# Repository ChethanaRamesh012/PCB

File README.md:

Designed a high-frequency PLL circuit on a two-layer PCB using KiCad, optimizing signal integrity and minimizing phase noise for RF 
applications.
Implemented precise trace routing, controlled impedance, and grounding strategies to enhance frequency stability and reduce 
electromagnetic interference (EMI).

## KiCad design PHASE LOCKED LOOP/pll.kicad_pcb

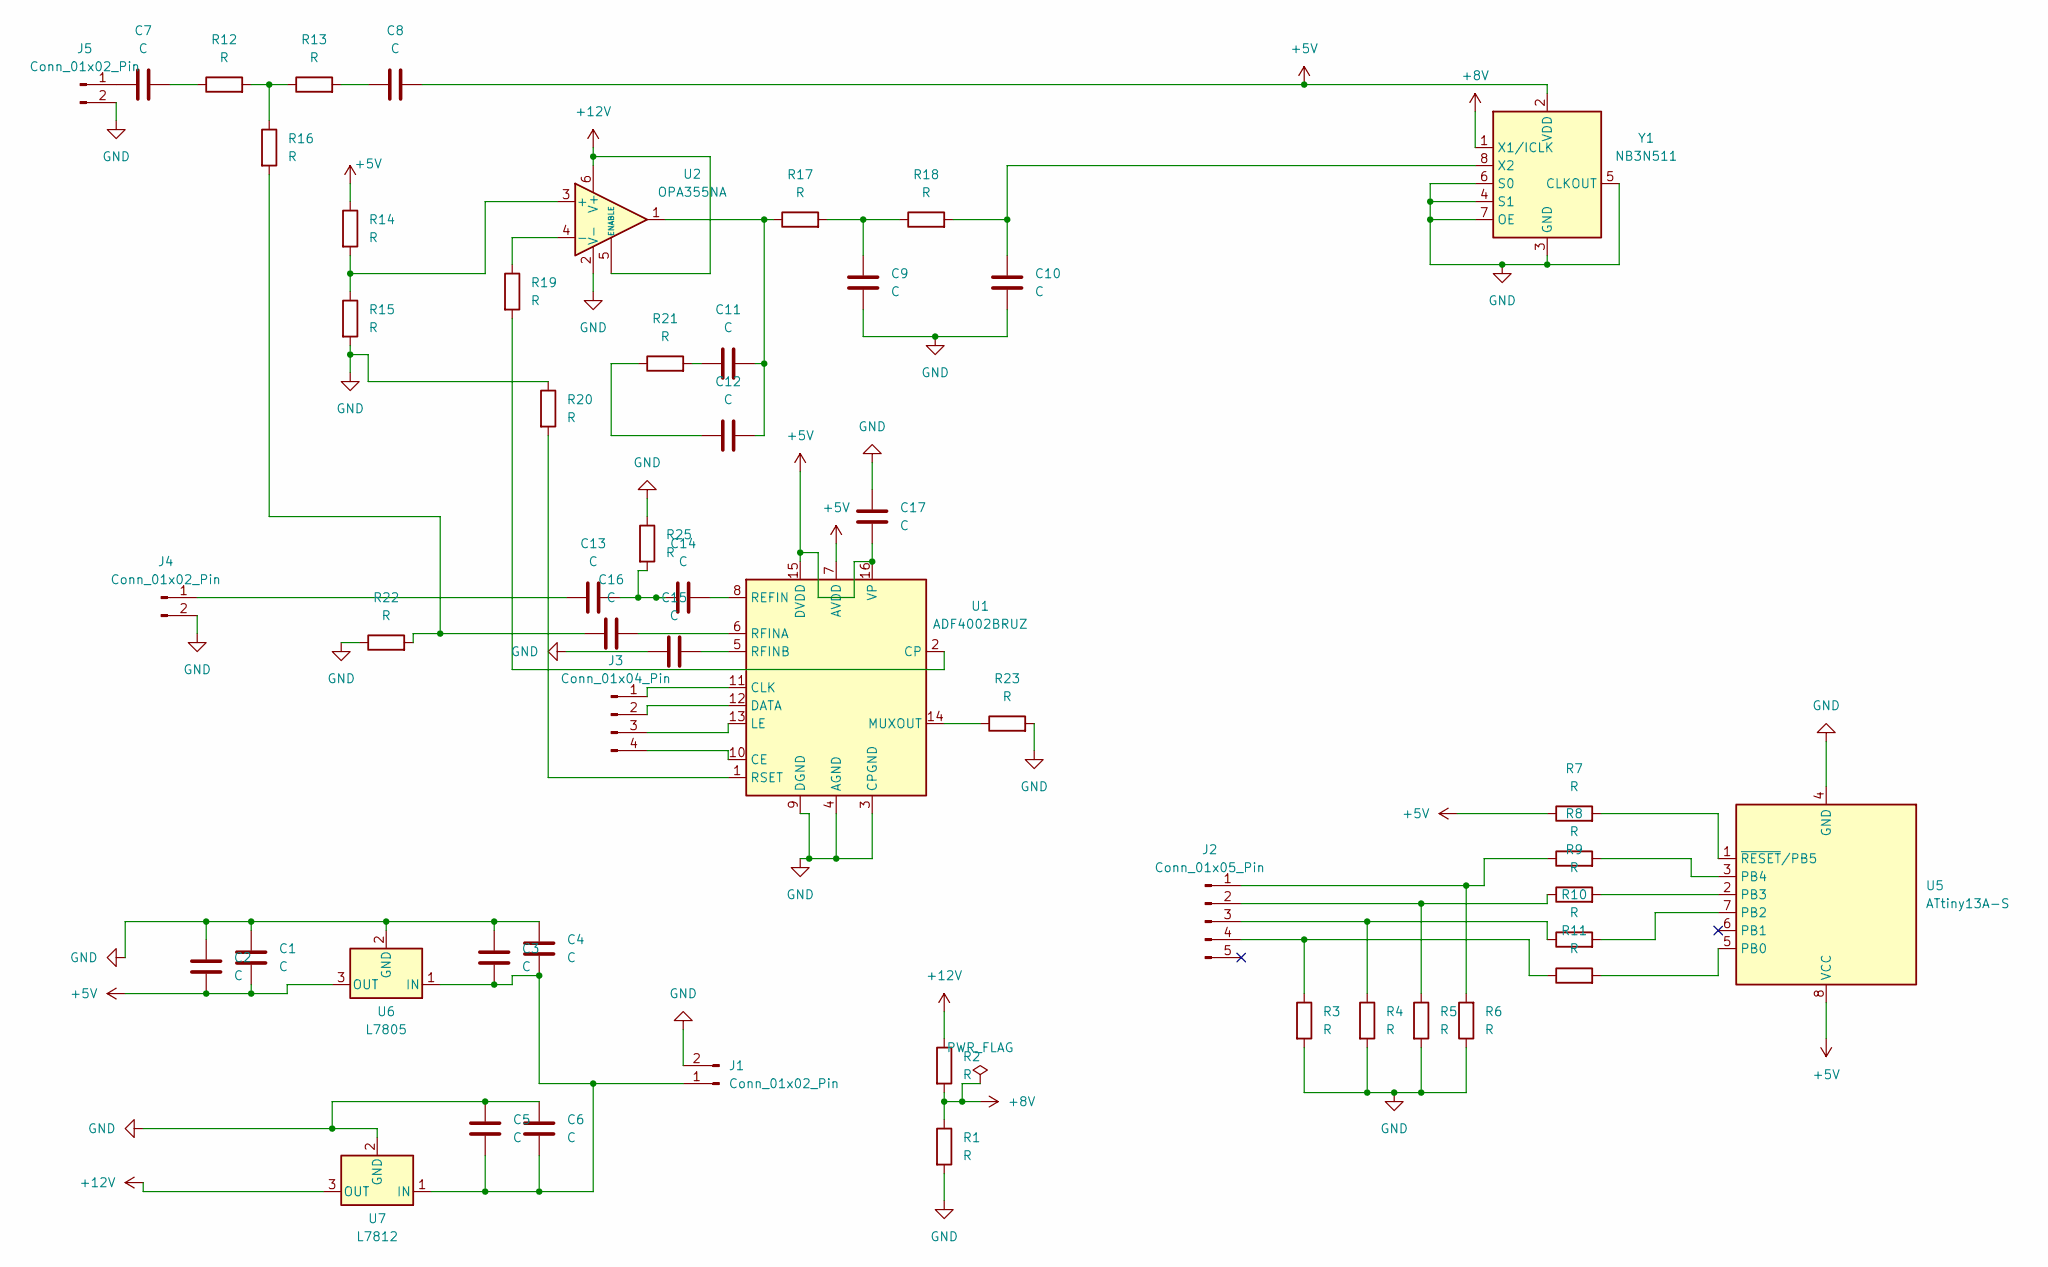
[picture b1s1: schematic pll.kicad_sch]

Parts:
C1, C2, C3, C4, C5, C6, C7, C8, C9, C10, C11, C12, C13, C14, C15, C16, C17: C; C_Axial_L3.8mm_D2.6mm_P7.50mm_Horizontal
J1: Conn_01x02_Pin; PinHeader_1x02_P2.00mm_Vertical
J2: Conn_01x05_Pin; PinHeader_1x05_P1.27mm_Vertical
J3: Conn_01x04_Pin; PinHeader_1x04_P1.00mm_Vertical
J4, J5: Conn_01x02_Pin; PinHeader_1x02_P1.00mm_Vertical
R1, R2, R3, R4, R5, R6, R7, R8, R9, R10, R11, R12, R13, R14, R15, R16, R17, R18, R19, R20, R21, R22, R23, R25: R; R_Axial_DIN0204_L3.6mm_D1.6mm_P1.90mm_Vertical
U1: ADF4002BRUZ; TSSOP-16_4.4x5mm_P0.65mm
U2: OPA355NA; SOT-23-6
U5: ATtiny13A-S; SOIC-8_5.3x5.3mm_P1.27mm
U6: L7805; TO-220F-3_Vertical
U7: L7812; TO-220F-3_Vertical
Y1: NB3N511; SOIC-8_3.9x4.9mm_P1.27mm

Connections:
+8V: R1.1, R2.2, Y1.1 (X1/ICLK)
+12V: R2.1, U2.5 (ENABLE), U2.6 (V+), U7.3 (OUT)
GND: C1.1, C2.1, C3.1, C4.1, C5.1, C6.1, C9.1, C10.1, C15.1, C17.2, J1.2, J4.2, J5.2, R1.2, R3.2, R4.2, R5.2, R6.1, R15.2, R20.1, R22.1, R23.2, R25.1, U1.3 (CPGND), U1.4 (AGND), U1.9 (DGND), U2.2 (V-), U5.4 (GND), U6.2 (GND), U7.2 (GND), Y1.3 (GND), Y1.4 (S1), Y1.5 (CLKOUT), Y1.6 (S0), Y1.7 (OE)
unnamed: C7.2, R12.1
unnamed: C8.1, R13.2
unnamed: C9.2, R17.2, R18.1
unnamed: C11.1, R21.2
unnamed: C11.2, C12.2, R17.1, U2.1
unnamed: C12.1, R21.1
unnamed: C13.2, C14.1, R25.2
unnamed: C16.1, R16.2, R22.2
unnamed: C3.2, C4.2, C5.2, C6.2, J1.1, U6.1 (IN), U7.1 (IN)
unnamed: J2.1, R6.2, R8.1
unnamed: J2.2, R5.1, R9.1
unnamed: J2.3, R4.1, R10.1
unnamed: J2.4, R3.1, R11.1
unnamed: J3.1, U1.11 (CLK)
unnamed: J3.2, U1.12 (DATA)
unnamed: J3.3, U1.13 (LE)
unnamed: J3.4, U1.10 (CE)
unnamed: C13.1, J4.1
unnamed: C7.1, J5.1
unnamed: R12.2, R13.1, R16.1
unnamed: R19.2, U1.2 (CP)
unnamed: R23.1, U1.14 (MUXOUT)
unnamed: C14.2, U1.8 (REFIN)
unnamed: C16.2, U1.6 (RFINA)
unnamed: C15.2, U1.5 (RFINB)
unnamed: R20.2, U1.1 (RSET)
unnamed: R14.2, R15.1, U2.3 (+)
unnamed: R19.1, U2.4 (-)
unnamed: R11.2, U5.5 (PB0)
unnamed: R10.2, U5.7 (PB2)
unnamed: R9.2, U5.2 (PB3)
unnamed: R8.2, U5.3 (PB4)
unnamed: R7.2, U5.1 (~RESET/PB5)
unnamed: C10.2, R18.2, Y1.8 (X2)

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
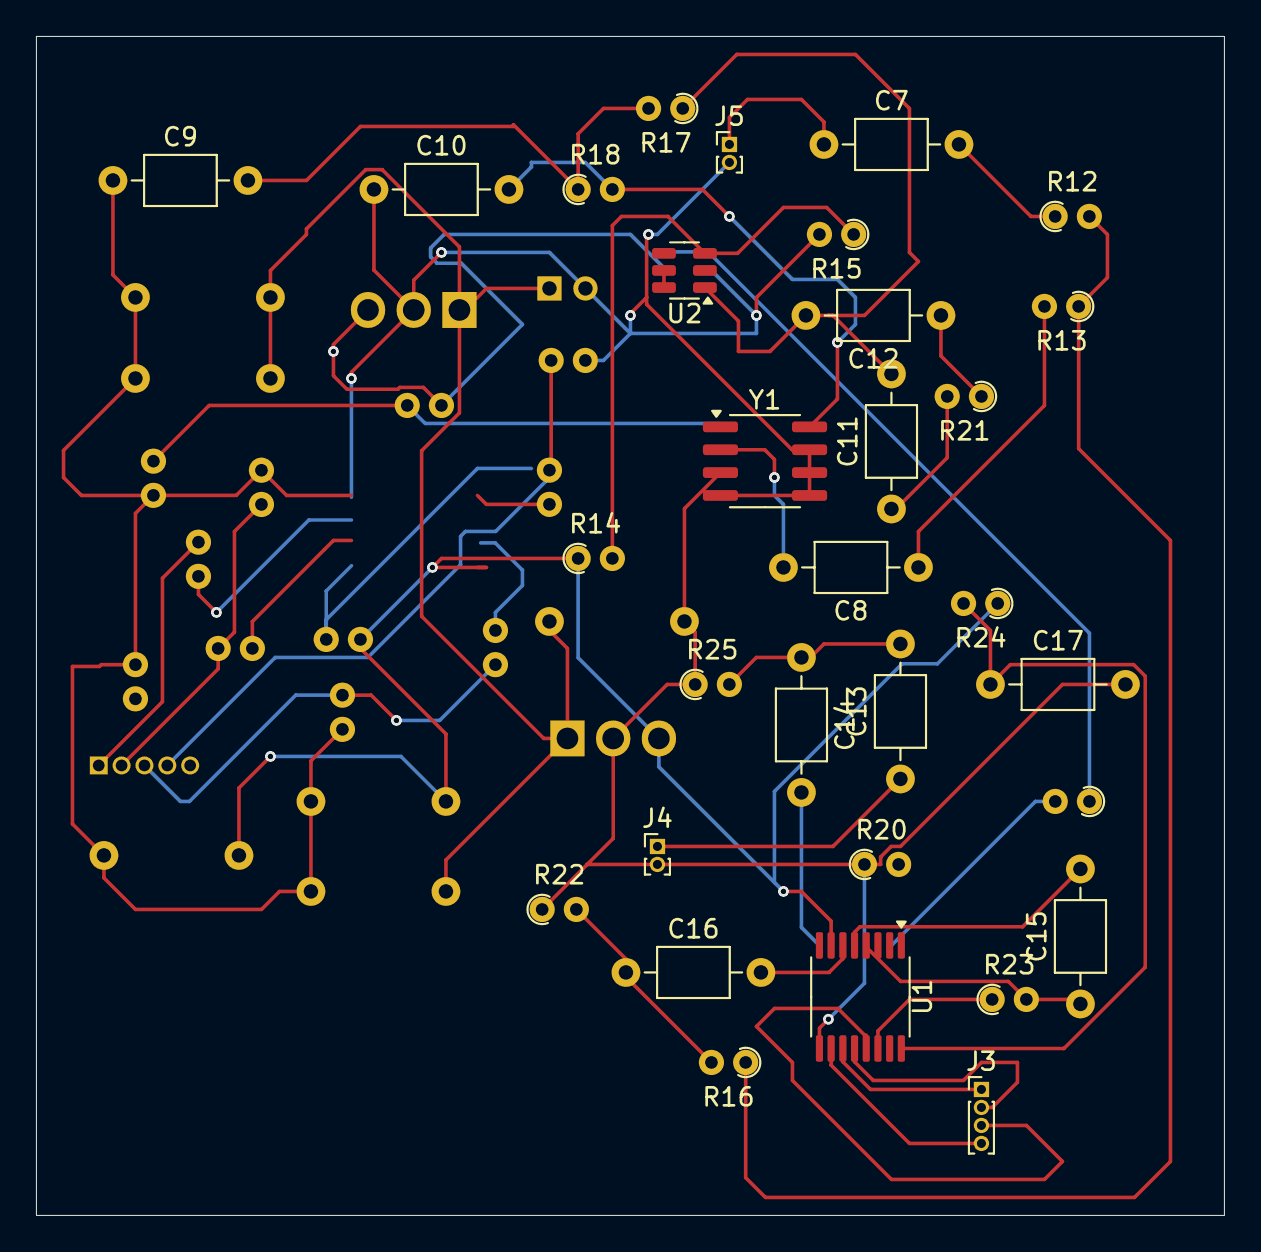
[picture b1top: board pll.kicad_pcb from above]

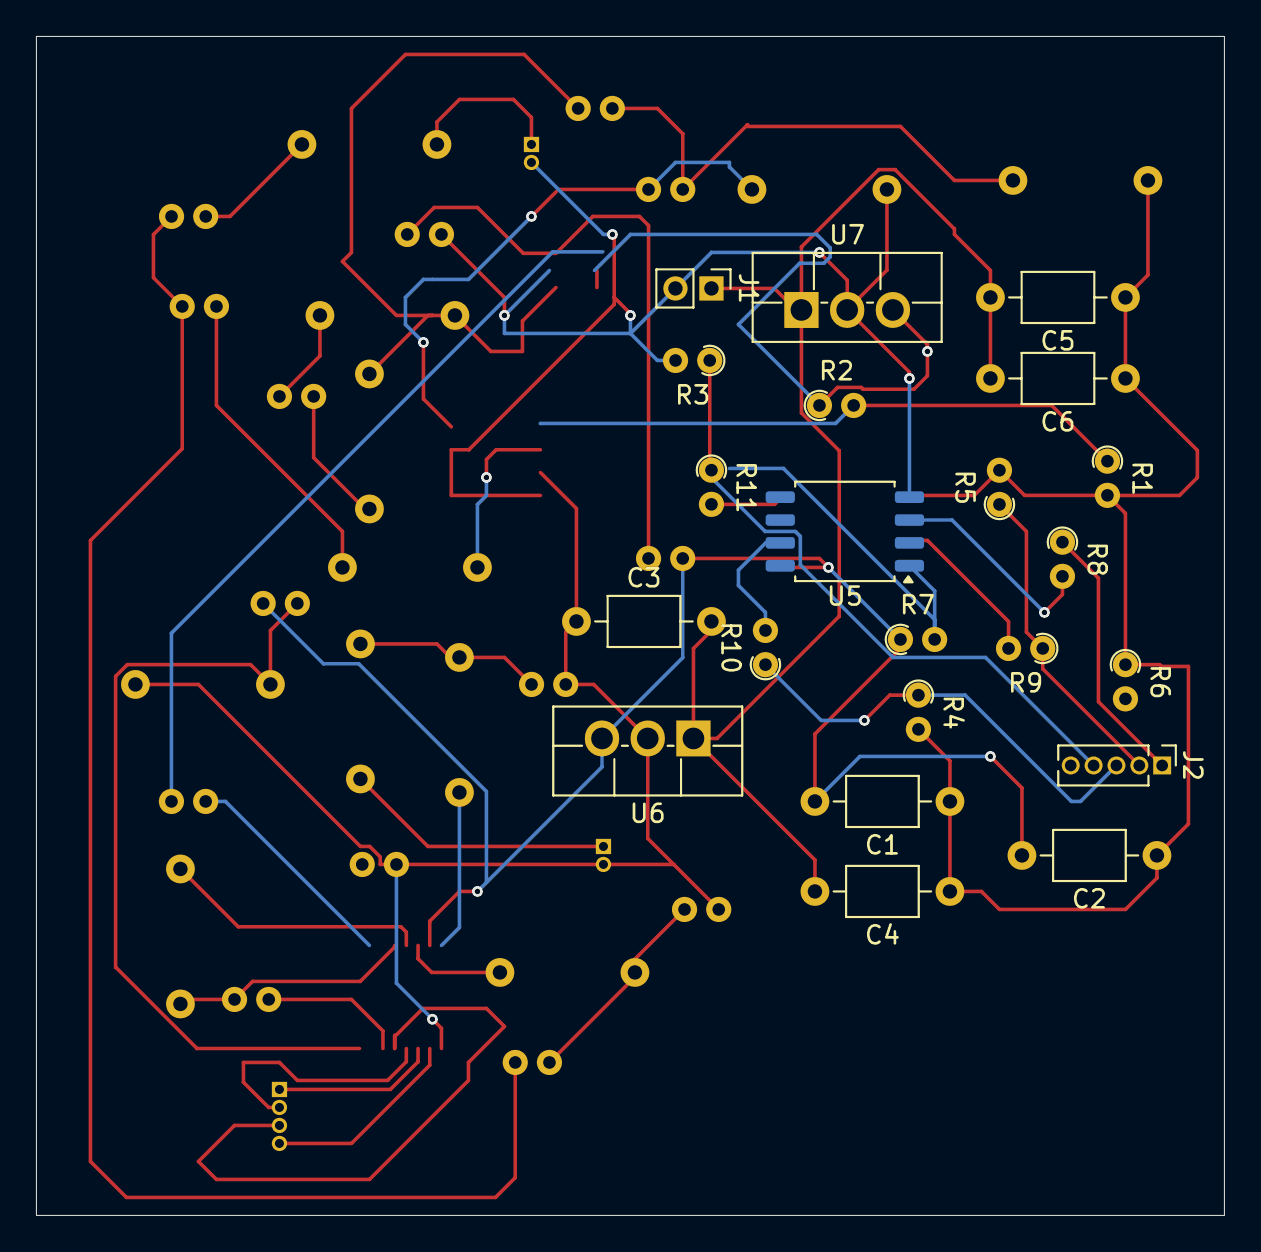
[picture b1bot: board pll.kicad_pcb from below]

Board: 2 copper layers, 66.0 x 65.5 mm, 53 parts (22 on the bottom side), 40 nets.

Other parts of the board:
R24: R; R_Axial_DIN0204_L3.6mm_D1.6mm_P1.90mm_Vertical

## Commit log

2025-04-05 Create PLL
    This file contains pcb and schematic
